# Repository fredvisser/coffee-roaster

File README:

# DIY Hot Air Coffee Roaster

I've been building controllers for modified hot air popcorn poppers for many years. This repository is my latest attempt to make home coffee roasting simple, reliable, scientific, and affordable.

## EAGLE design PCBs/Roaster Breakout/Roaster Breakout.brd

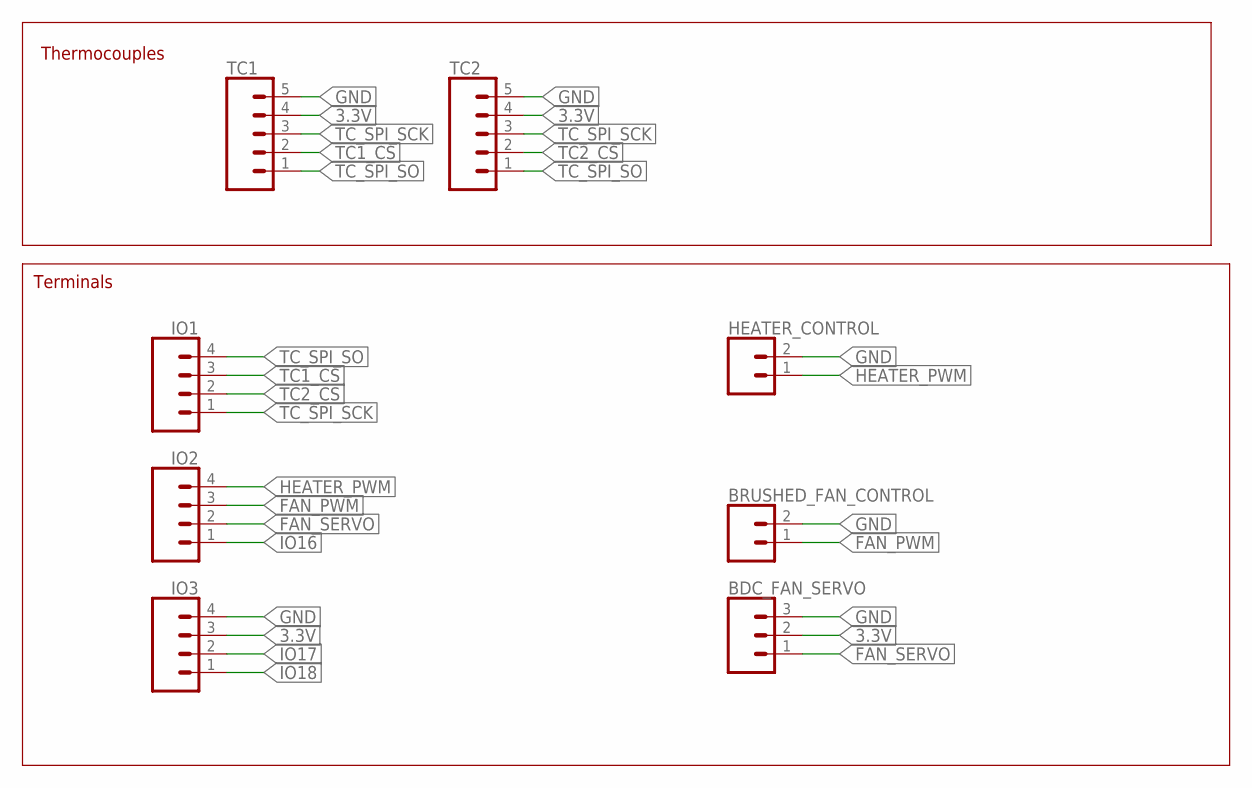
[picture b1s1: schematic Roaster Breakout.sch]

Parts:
BDC_FAN_SERVO: CONN_03LONGPADS; 1X03_LONGPADS
BRUSHED_FAN_CONTROL: CONN_02PTH3; 1X02_LONGPADS
HEATER_CONTROL: CONN_02PTH3; 1X02_LONGPADS
IO1, IO2, IO3: CONN_04LONGPADS; 1X04_LONGPADS
TC1, TC2: CONN_05PTH_LONGPADS; 1X05_LONGPADS

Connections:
3.3V: BDC_FAN_SERVO.2, IO3.3, TC1.4, TC2.4
FAN_PWM: BRUSHED_FAN_CONTROL.1, IO2.3
FAN_SERVO: BDC_FAN_SERVO.1, IO2.2
GND: BDC_FAN_SERVO.3, BRUSHED_FAN_CONTROL.2, HEATER_CONTROL.2, IO3.4, TC1.5, TC2.5
HEATER_PWM: HEATER_CONTROL.1, IO2.4
IO16: IO2.1
IO17: IO3.2
IO18: IO3.1
TC1_CS: IO1.3, TC1.2
TC2_CS: IO1.2, TC2.2
TC_SPI_SCK: IO1.1, TC1.3, TC2.3
TC_SPI_SO: IO1.4, TC1.1, TC2.1

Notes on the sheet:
Thermocouples
Terminals

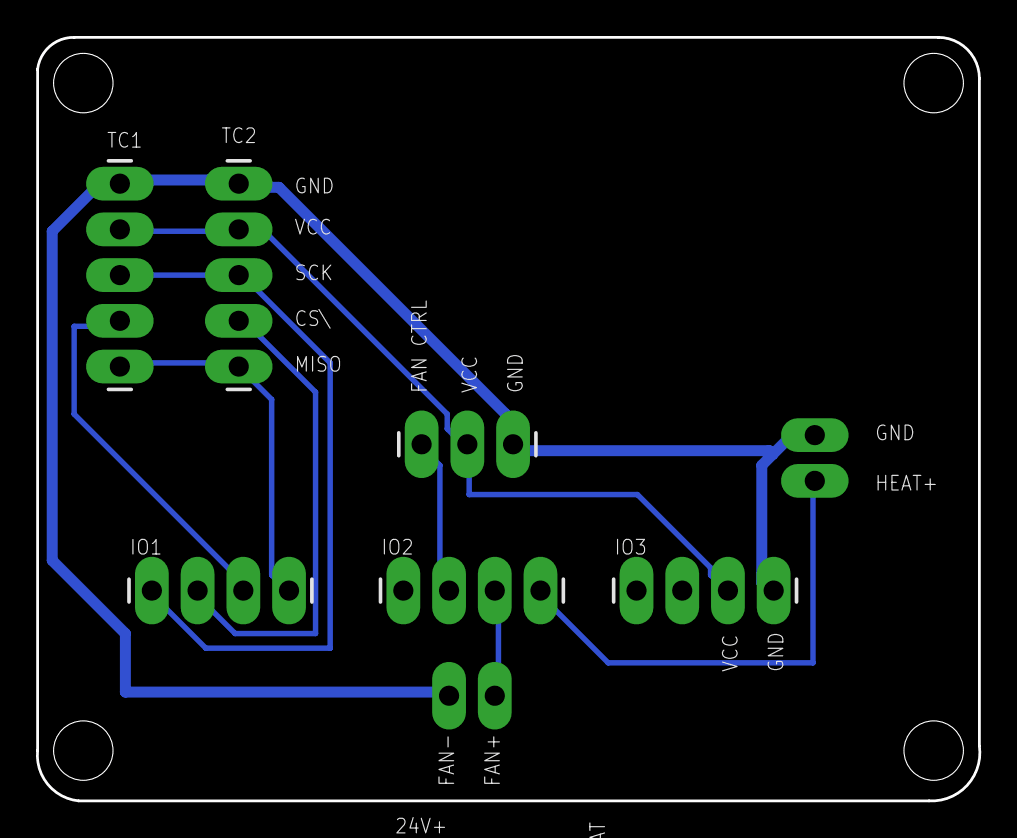
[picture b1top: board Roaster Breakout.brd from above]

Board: 2 copper layers, 52.4 x 42.4 mm, 9 parts (0 on the bottom side), 9 nets.

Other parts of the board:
U$1: LOGO

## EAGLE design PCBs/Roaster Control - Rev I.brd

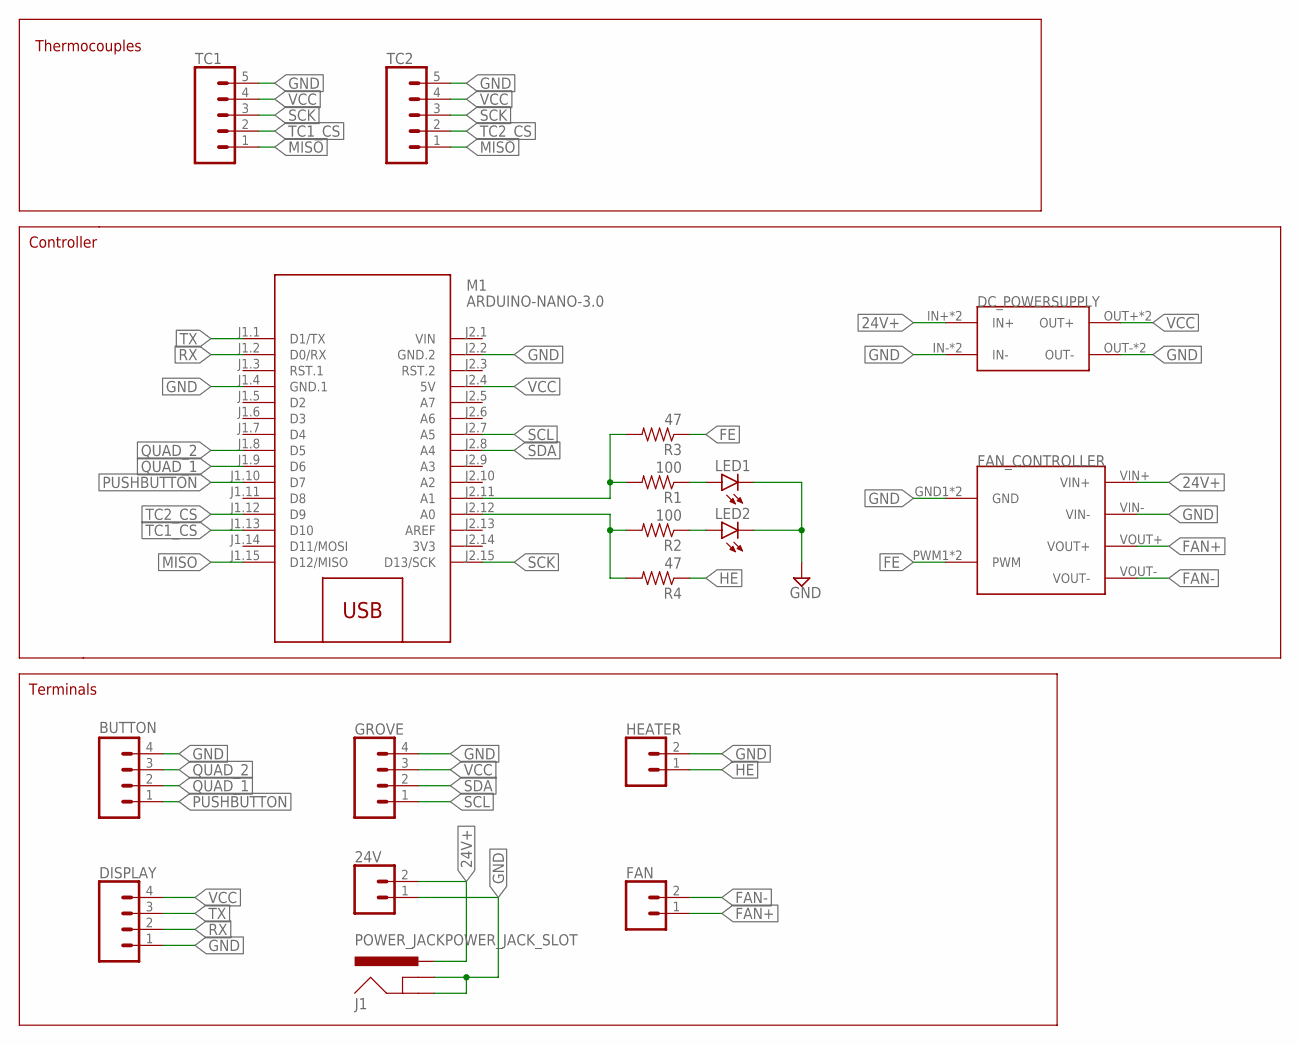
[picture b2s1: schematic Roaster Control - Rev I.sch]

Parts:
24V: CONN_02PTH3; 1X02_LONGPADS
BUTTON: M04LONGPADS; 1X04_LONGPADS
DC_POWERSUPPLY: DCDC; DCDC_FP
DISPLAY: CONN_04LONGPADS; 1X04_LONGPADS
FAN: CONN_02PTH3; 1X02_LONGPADS
FAN_CONTROLLER: DC_MC; DC_MC_FP
GROVE: CONN_04LONGPADS; 1X04_LONGPADS
HEATER: CONN_02PTH3; 1X02_LONGPADS
J1: POWER_JACKPOWER_JACK_SLOT; POWER_JACK_PTH_SLOT
LED1, LED2: LEDCHIP-LED0805; CHIP-LED0805
M1: ARDUINO-NANO-3.0
R1, R2: 100; 0603
R3, R4: 47; 0603
TC1, TC2: CONN_05PTH_LONGPADS; 1X05_LONGPADS

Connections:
3V3: M1.J2.14 (3V3)
24V+: 24V.2, DC_POWERSUPPLY.IN+, DC_POWERSUPPLY.IN+2 (IN+), FAN_CONTROLLER.VIN+, J1.PWR
FAN+: FAN.1, FAN_CONTROLLER.VOUT+
FAN-: FAN.2, FAN_CONTROLLER.VOUT-
FAN_EN: M1.J2.11 (A1), R1.2, R3.2
FE: FAN_CONTROLLER.PWM1 (PWM), FAN_CONTROLLER.PWM2 (PWM), R3.1
GND: 24V.1, BUTTON.4, DC_POWERSUPPLY.IN-, DC_POWERSUPPLY.IN-2 (IN-), DC_POWERSUPPLY.OUT-, DC_POWERSUPPLY.OUT-2 (OUT-), DISPLAY.1, FAN_CONTROLLER.GND1 (GND), FAN_CONTROLLER.GND2 (GND), FAN_CONTROLLER.VIN-, GROVE.4, HEATER.2, J1.GND, J1.GNDBREAK, LED1.C, LED2.C, M1.J1.4 (GND.1), M1.J2.2 (GND.2), TC1.5, TC2.5
HE: HEATER.1, R4.1
HEAT_EN: M1.J2.12 (A0), R2.2, R4.2
MISO: M1.J1.15 (D12/MISO), TC1.1, TC2.1
unnamed: LED1.A, R1.1
unnamed: LED2.A, R2.1
PUSHBUTTON: BUTTON.1, M1.J1.10 (D7)
QUAD_1: BUTTON.2, M1.J1.9 (D6)
QUAD_2: BUTTON.3, M1.J1.8 (D5)
RX: DISPLAY.2, M1.J1.2 (D0/RX)
SCK: M1.J2.15 (D13/SCK), TC1.3, TC2.3
SCL: GROVE.1, M1.J2.7 (A5)
SDA: GROVE.2, M1.J2.8 (A4)
TC1_CS: M1.J1.13 (D10), TC1.2
TC2_CS: M1.J1.12 (D9), TC2.2
TX: DISPLAY.3, M1.J1.1 (D1/TX)
VCC: DC_POWERSUPPLY.OUT+, DC_POWERSUPPLY.OUT+2 (OUT+), DISPLAY.4, GROVE.3, M1.J2.4 (5V), TC1.4, TC2.4
VIN: M1.J2.1 (VIN)

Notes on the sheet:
Thermocouples
Terminals
Controller

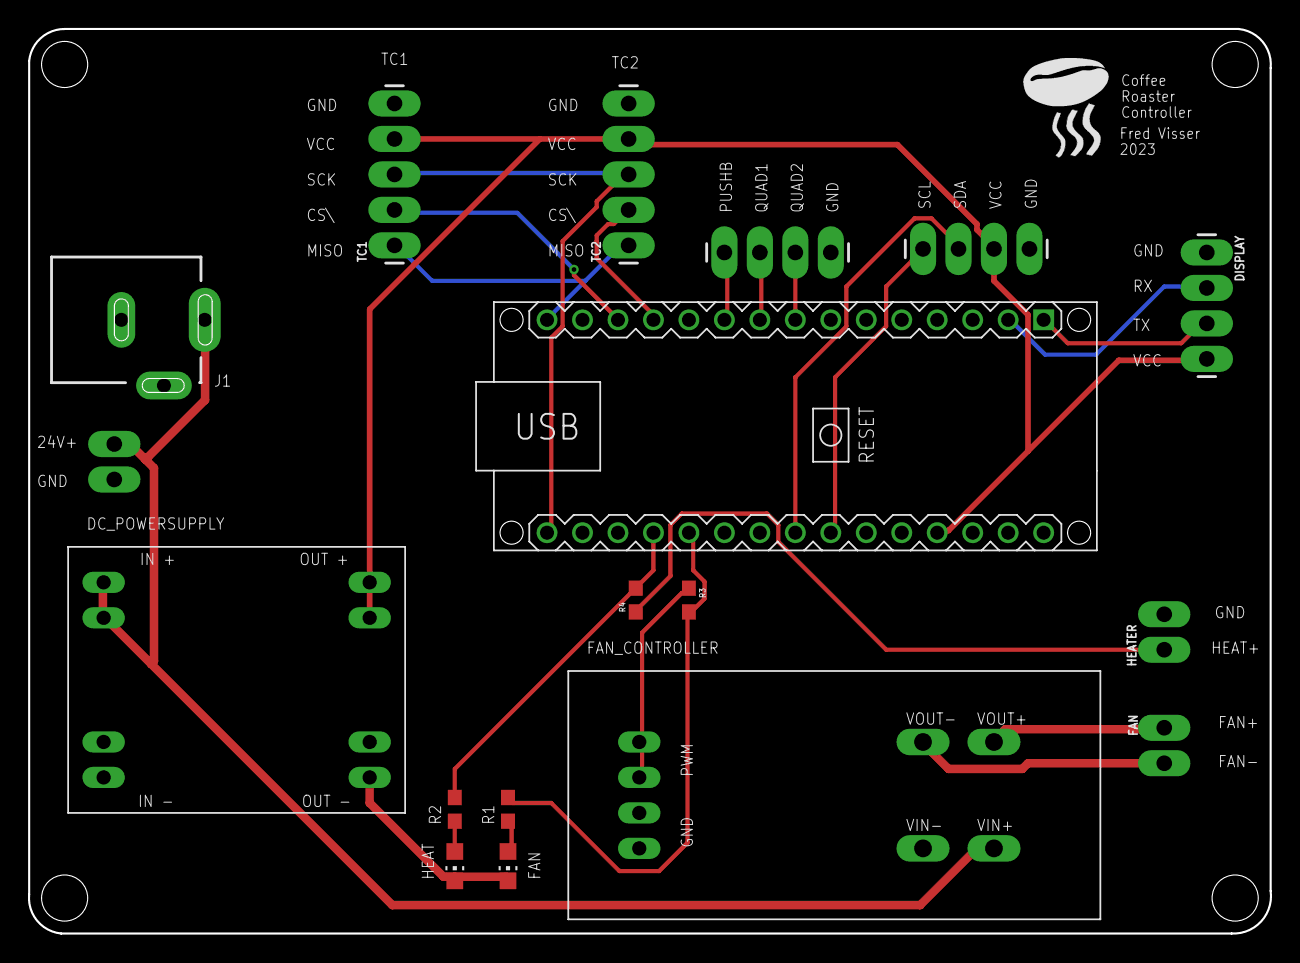
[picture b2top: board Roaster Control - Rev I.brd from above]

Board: 2 copper layers, 88.9 x 64.8 mm, 19 parts (0 on the bottom side), 22 nets.

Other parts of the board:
U$1: LOGO

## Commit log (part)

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2024-01-12 Initial controller firmware
2024-01-12 Add WebSocket support for Artisan SW
2024-01-21 refactor and support interpolated temp profiles
2024-01-23 add PID control
2024-01-23 Readme updates
2024-01-28 Refactor code, add tests, add GUI wifi config
2024-01-28 Nextion display update
2024-01-29 Add PCB files and readme updates
2024-01-30 remove wifi credentials via Settings.h file
2024-09-11 3d printing files
2024-12-11 Assembly instructions and IDE migration
2024-12-11 fix video
2024-12-11 smaller video
2025-09-19 add bdc and disable OTA
2025-12-22 BDC motor support + testing
2025-12-22 pipeline fix
2025-12-22 add readme and license - build fix
2025-12-22 add remaining dependencies to build
2025-12-22 build warning fixes
2025-12-23 test and script improvements
2025-12-24 console web app
2025-12-24 various refactoring changes
2025-12-25 Nextion ProfileActive improvements: plot full profile on waveform (480x170) with component ID 2, corrected x-axis orientation; seed and honor final temp override via Nextion; add trigger4() to plot o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
2025-12-26 working profile management
2025-12-27 loading screen
2026-04-11 fix: autotuner tweaks
2026-04-16 add SystemLink publishing support
2026-05-04 feat: onset dead time autotuner + remove sawtooth tuner
    Step-response autotuner improvements:
    - Add onset dead time detector (3σ noise threshold) for more accurate
    SIMC tuning on higher-order thermal systems where FOPDT dead time is
    inflated. Uses measured response onset instead of model-fitted θ.
    - Populate feedforward model parameters (heaterCoeff, coolingCoeff,
    drift) from FOPDT model in both autotuner paths, fixing broken
2026-05-04 feat: add agent skills, web UI updates, tests, and SystemLink notebooks
    Agent skills:
    - nipkg-file-package: NI Package Manager file packaging
    - slcli: SystemLink CLI reference (refactored with sub-references)
    - systemlink-job-debugging: Salt job debugging guide
    - systemlink-notebook: Jupyter notebook creation for SystemLink
    - systemlink-python-test: Python test integration with SystemLink
2026-05-04 remove conversion notebook
2026-05-04 fix: remove test_validation.ino (references non-existent PIDValidation.hpp and sawtooth APIs)
2026-05-04 ci: cache Arduino deps and avoid duplicate builds
2026-05-04 fix: safety-critical firmware issues and test correctness
    Safety fixes (roaster-firmware.ino):
    - enterCoolingState(): immediately kill heater via digitalWrite(HEATER, LOW)
    and heaterRelay.setPWM(0) before any state changes, closing 500ms window
    where heater could remain active after roasting ends
    - trigger2(): add temperature guard - reject cooling skip if temp > 160F,
    properly shut down fans/BDC on transition to IDLE
2026-05-04 fix(ci): add --overwrite to arduino-cli config init
    Cache restore of ~/.arduino15 causes 'Config file already exists' error.
    Adding --overwrite ensures a fresh config is created regardless.
2026-05-07 feat: add GitHub Pages project site
2026-05-07 fix: enable GitHub Pages bootstrapping
2026-05-08 refine: simplify project site and use Node 22
2026-05-08 fix: make Arduino CLI config init idempotent
2026-05-08 redesign: clean project page with categorized content and parts list
    - Replace marketing-heavy copy with direct project descriptions
    - Add categorized 'What's in the repo' cards (3D printing, PCB, firmware, popper mod)
    - Add full parts list table with purchase links
    - Switch to Inter font, minimal borders, no decorative effects
    - Use real build photos throughout
    - Add safety section and build steps with numbered layout
2026-05-12 resolve workspace bug
2026-06-03 first draft
2026-06-04 reorganization and cleanup
2026-06-07 Add LVGL UI refresh and local simulator
2026-06-19 print files, firmware bringup, testing
2026-06-19 cleanup and doc update
2026-06-19 site cleanup
2026-06-19 Tighten v2 documentation consistency
2026-06-19 improved error handling
2026-06-19 failure display improvements
2026-06-19 failure mode updates
2026-06-19 better mobile support
2026-06-19 pipeline fixes
2026-06-19 pipeline fixes 2
2026-06-19 pipeline fixes 3
2026-06-19 pipeline fixes 4
2026-06-19 pipeline fixes 5
2026-06-20 site updates and pcb labeling

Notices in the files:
parts and their libraries:
SparkFun-Connectors: Licensing: Creative Commons ShareAlike 4.0 International - https://creativecommons.org/licenses/by-sa/4.0
SparkFun: Licensing: CC v3.0 Share-Alike You are welcome to use this library for commercial purposes.
